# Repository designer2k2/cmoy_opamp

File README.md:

# cmoy_opamp
flexible cmoy style headphone amplifier

it can fit dual or single Op Amp´s, even a ZIF socket is possible for fast Op Amp changes.

## The schematics:

It looks a bit strange, but its to fit both SMD and THT parts, and the different Op Amps.

One selection was made specifically, thats the virtual ground with a resistor voltage divider and voltage follower with the LMH6642. Like this it adds another Op Amp, fitting the Op Amp challenge better.

## PCB:

its made to fit single or dual Op Amps:

To listen to many different IC´s a ZIF Socket is helpful:

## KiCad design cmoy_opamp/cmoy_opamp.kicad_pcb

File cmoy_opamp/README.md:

# kicad-cmoy
cmoy headphone amplifier in kicad

## Schematic:

Created by http://www.designer2k2.at

## Details:
cmoy is a simple but great headphone amplifier, original creator: http://headwize.com/?page_id=707

Here is a working archived copy from the headwize website: http://web.archive.org/web/20150415003947/http://headwize.com/?page_id=707

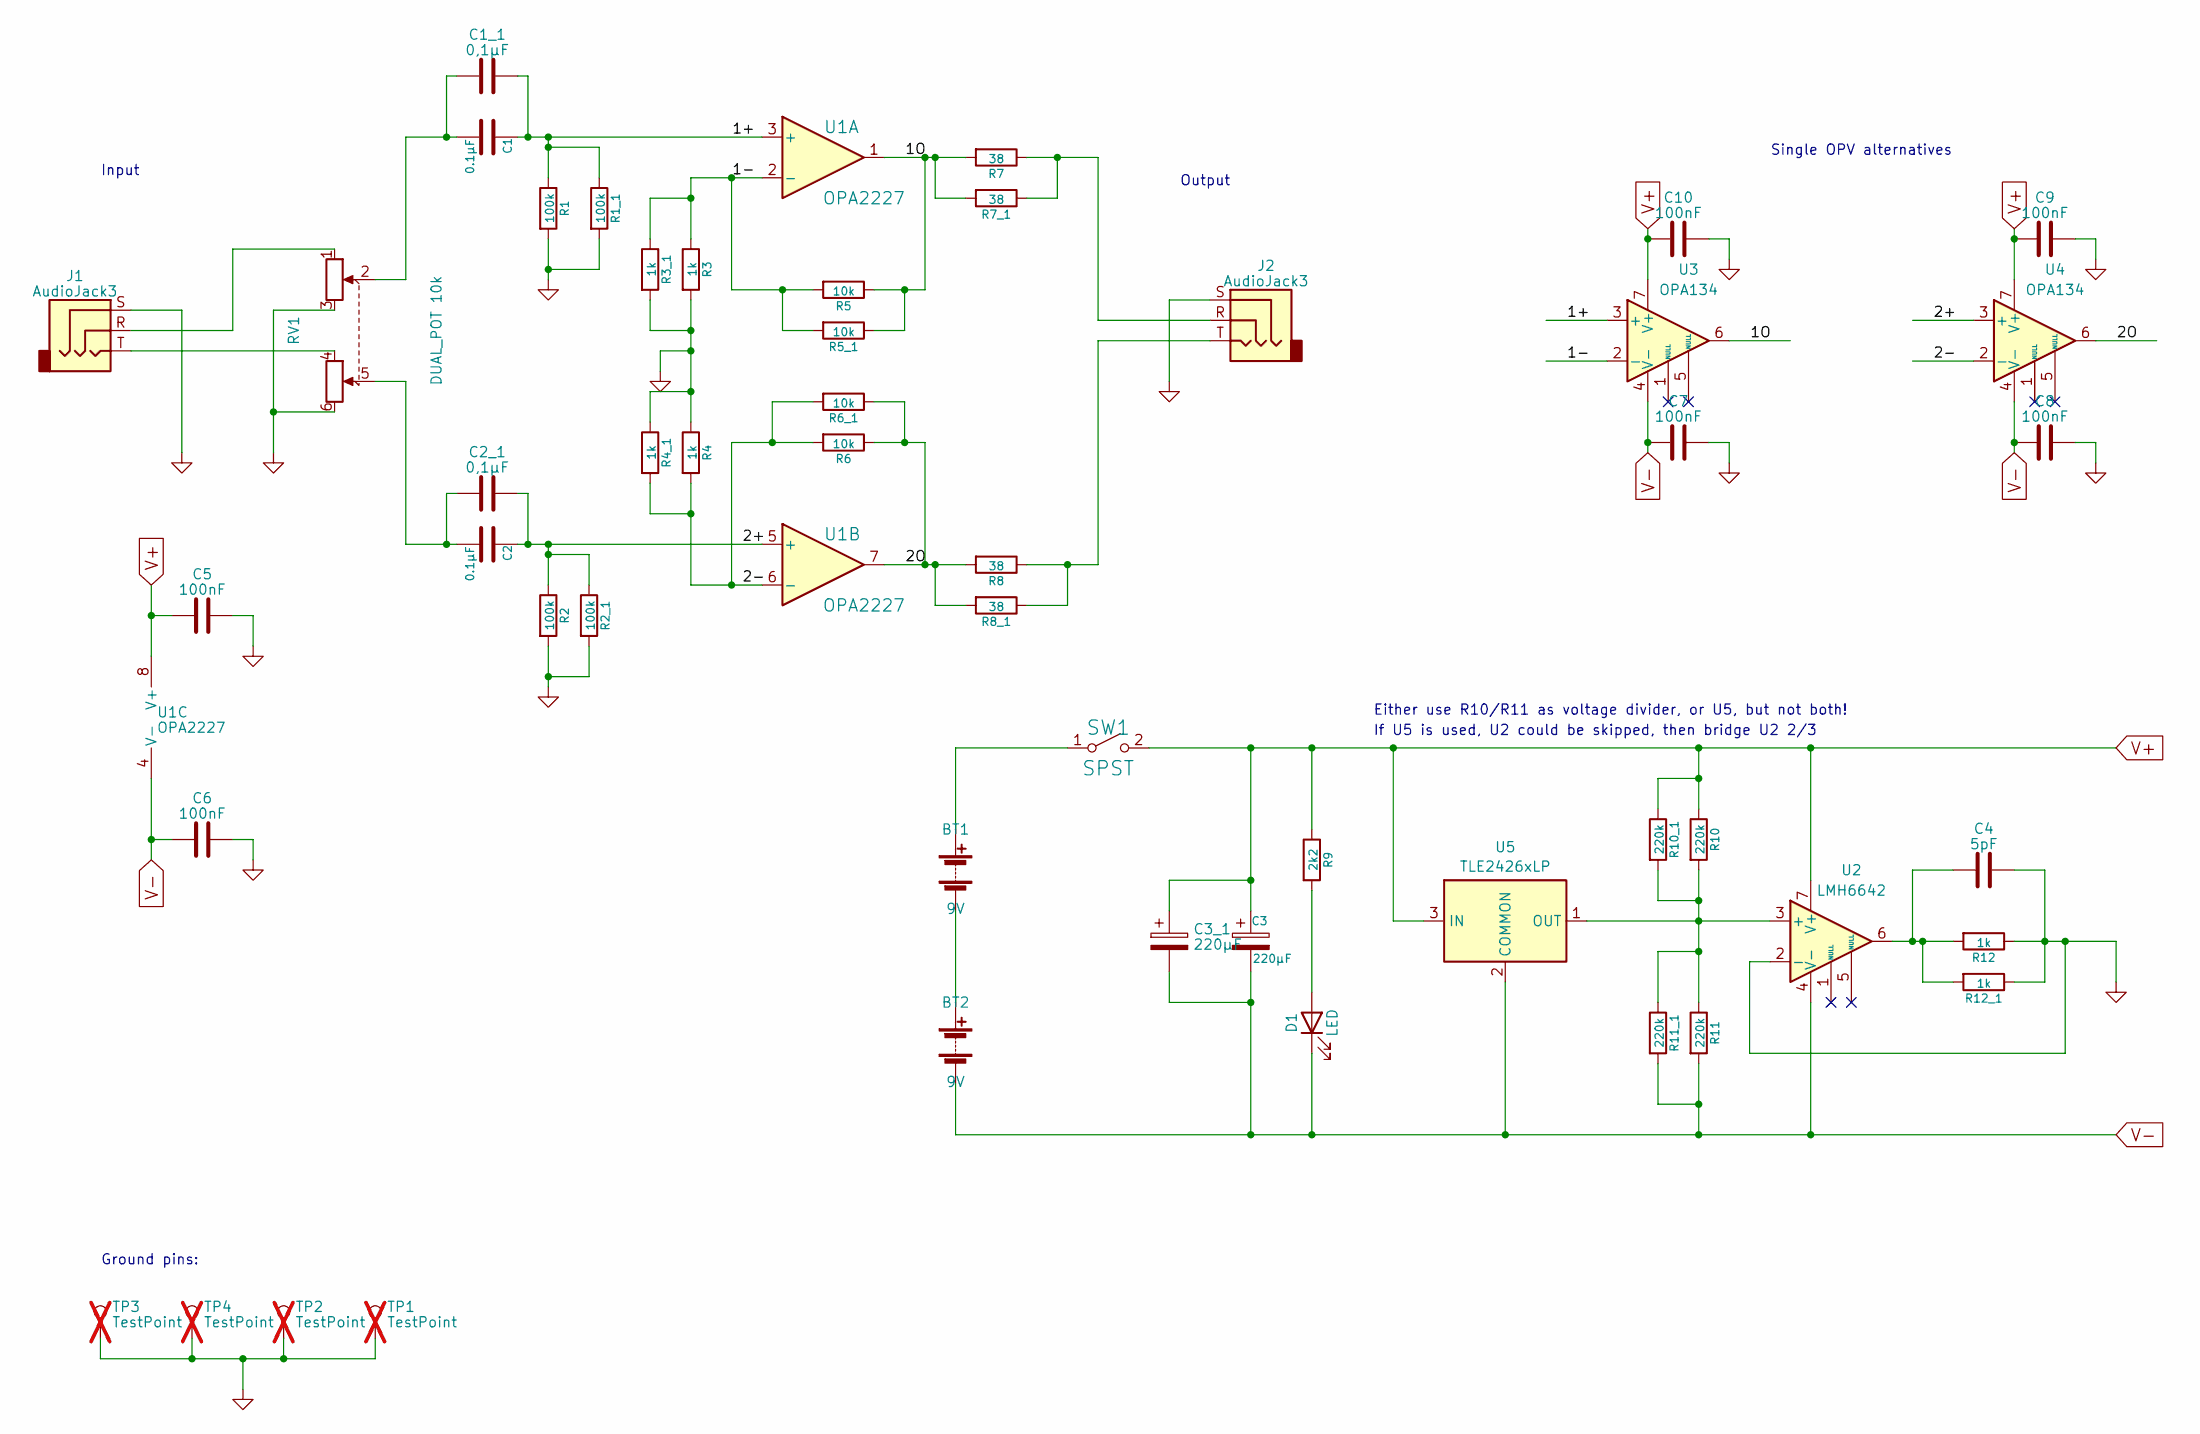
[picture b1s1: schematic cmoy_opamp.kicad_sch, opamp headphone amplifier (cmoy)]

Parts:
BT1, BT2: 9V; PinHeader_2x01_P2.54mm_Vertical
C1, C2: 0.1µF; CP_Axial_L20.0mm_D10.0mm_P26.00mm_Horizontal; Part MKT1813410405
C1_1, C2_1: 0,1µF; C_Rect_L7.0mm_W6.0mm_P5.00mm; Part BFC237011105
C3: 220µF; CP_Elec_8x10
C3_1: 220µF; CP_Radial_D10.0mm_P3.50mm
C4: 5pF; C_1206_3216Metric
C5, C6, C7, C8, C9, C10: 100nF; C_1206_3216Metric
D1: LED; LED_1206_3216Metric
J1, J2: AudioJack3; Jack_3.5mm_CUI_SJ1-3523N_Horizontal; Part SJ1-3523N
R1, R2: 100k; R_1206_3216Metric
R1_1, R2_1: 100k; R_Axial_DIN0204_L3.6mm_D1.6mm_P7.62mm_Horizontal
R3, R4, R12: 1k; R_1206_3216Metric
R3_1, R4_1, R12_1: 1k; R_Axial_DIN0204_L3.6mm_D1.6mm_P7.62mm_Horizontal
R5, R6: 10k; R_1206_3216Metric
R5_1, R6_1: 10k; R_Axial_DIN0204_L3.6mm_D1.6mm_P7.62mm_Horizontal
R7, R8: 38; R_1206_3216Metric
R7_1, R8_1: 38; R_Axial_DIN0204_L3.6mm_D1.6mm_P7.62mm_Horizontal
R9: 2k2; R_1206_3216Metric
R10, R11: 220k; R_1206_3216Metric
R10_1, R11_1: 220k; R_Axial_DIN0204_L3.6mm_D1.6mm_P7.62mm_Horizontal
RV1: DUAL_POT 10k; Potentiometer_Alps_RK097_Dual_Horizontal; Part RK09712200HA
SW1: SPST; SW_CuK_OS102011MA1QN1_SPDT_Angled; Part OS102011MA1QN1
TP1, TP2, TP3, TP4: TestPoint; PinSocket_1x01_P2.54mm_Vertical; not fitted
U1: OPA2227; DIP-8_W7.62mm_Socket
U2: LMH6642; SOIC-8_3.9x4.9mm_P1.27mm; Part LMH6642MA
U3, U4: OPA134; DIP-8_W7.62mm_Socket
U5: TLE2426xLP; TO-92

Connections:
/1+: C1.1, C1_1.2, R1.1, R1_1.1, U1.3 (+), U3.3 (+)
/1-: R3.1, R3_1.1, R5.2, R5_1.2, U1.2 (-), U3.2 (-)
/1O: R5.1, R5_1.1, R7.2, R7_1.2, U1.1, U3.6
/2+: C2.1, C2_1.2, R2.1, R2_1.1, U1.5 (+), U4.3 (+)
/2-: R4.2, R4_1.2, R6.2, R6_1.2, U1.6 (-), U4.2 (-)
/2O: R6.1, R6_1.1, R8.2, R8_1.2, U1.7, U4.6
GND: C4.2, C5.2, C6.2, C7.2, C8.2, C9.2, C10.2, J1.S, J2.S, R1.2, R1_1.2, R2.2, R2_1.2, R3.2, R3_1.2, R4.1, R4_1.1, R12.1, R12_1.1, RV1.3, RV1.6, TP1.1, TP2.1, TP3.1, TP4.1, U2.2 (-)
unnamed: BT1.1 (+), SW1.1 (A)
unnamed: BT1.2 (-), BT2.1 (+)
unnamed: C1.2, C1_1.1, RV1.2
unnamed: C2.2, C2_1.1, RV1.5
unnamed: C4.1, R12.2, R12_1.2, U2.6
unnamed: D1.2 (A), R9.2
unnamed: J1.R, RV1.1
unnamed: J1.T, RV1.4
unnamed: J2.R, R7.1, R7_1.1
unnamed: J2.T, R8.1, R8_1.1
unnamed: R10.2, R10_1.2, R11.1, R11_1.1, U2.3 (+), U5.1 (OUT)
V+: C3.1, C3_1.1, C5.1, C9.1, C10.1, R9.1, R10.1, R10_1.1, SW1.2 (B), U1.8 (V+), U2.7 (V+), U3.7 (V+), U4.7 (V+), U5.3 (IN)
V-: BT2.2 (-), C3.2, C3_1.2, C6.1, C7.1, C8.1, D1.1 (K), R11.2, R11_1.2, U1.4 (V-), U2.4 (V-), U3.4 (V-), U4.4 (V-), U5.2 (COMMON)

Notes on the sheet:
If U5 is used, U2 could be skipped, then bridge U2 2/3
Input
Single OPV alternatives
Either use R10/R11 as voltage divider, or U5, but not both!
Ground pins:
Output

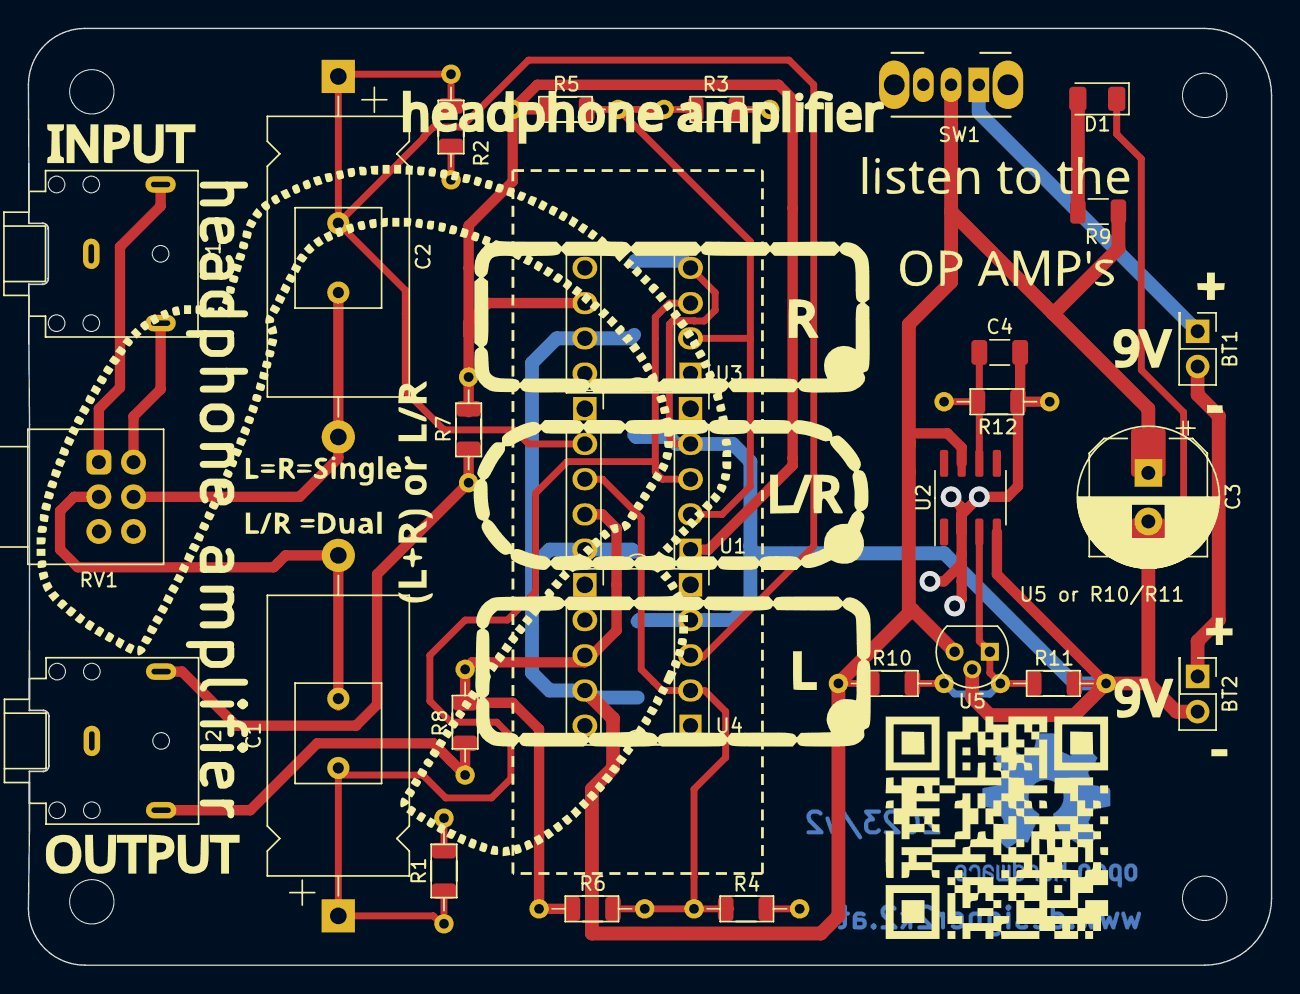
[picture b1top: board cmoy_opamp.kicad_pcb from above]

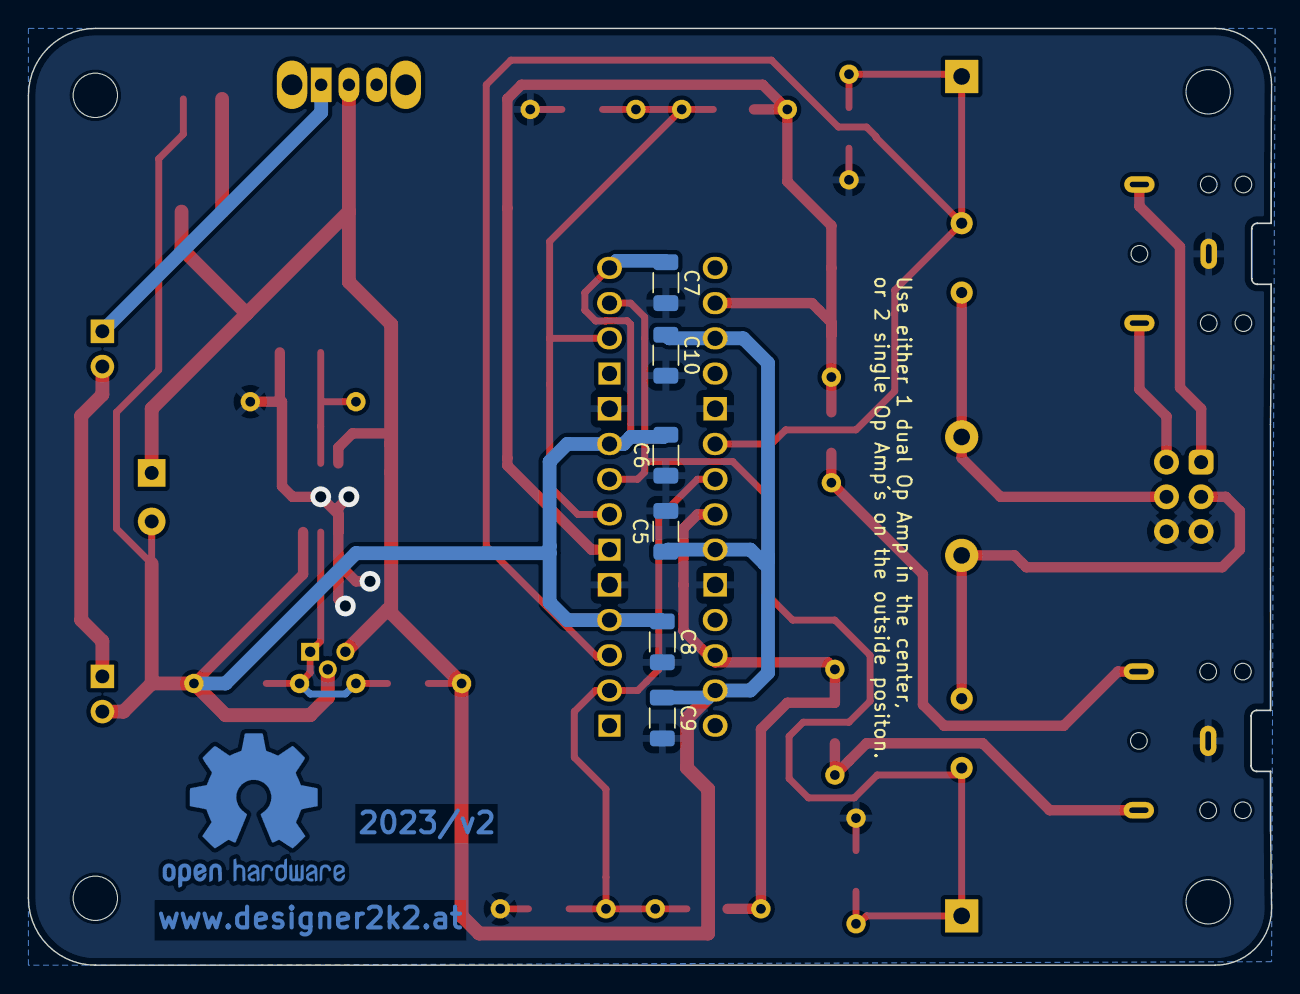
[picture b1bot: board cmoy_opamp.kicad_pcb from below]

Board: 2 copper layers, 89.7 x 67.6 mm, 52 parts (6 on the bottom side), 20 nets.

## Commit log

2023-04-23 schematic and intial parts placement
2023-04-23 Schematic´s as PDF and SVG
2023-04-27 dual footprint, THT and SMD, first layouting
2023-05-01 PCB Layout complete
2023-05-01 PCB art added
2023-05-01 PCB Version ready to order
2023-05-03 Documentation files updated
2023-05-09 replace some rescue lib symbols with built in ones
2023-05-13 fully remove rescue lib reference
2023-05-13 better 3D image
    - all 3d models added
    - use the raytracing option with floor
2023-05-13 add ZIF image
2023-05-16 Bugfix ZIF socket against R3/4/5/6
    Moving R3/3/4/5/6 a bit to the outside to have clearance for the ZIF socket.
    Like this the ZIF socket can sit flush and does not need to be stacked on DIL socket´s.
2023-09-04 change drilling to fit zif socket
    0,8mm increased to 1,1mm to fit the 0,9mm ZIF socket pins
2023-09-06 add build up image
2023-09-16 Add TLE2426 as option
    TLE2426 option alternative to R10/R11 voltage divider
